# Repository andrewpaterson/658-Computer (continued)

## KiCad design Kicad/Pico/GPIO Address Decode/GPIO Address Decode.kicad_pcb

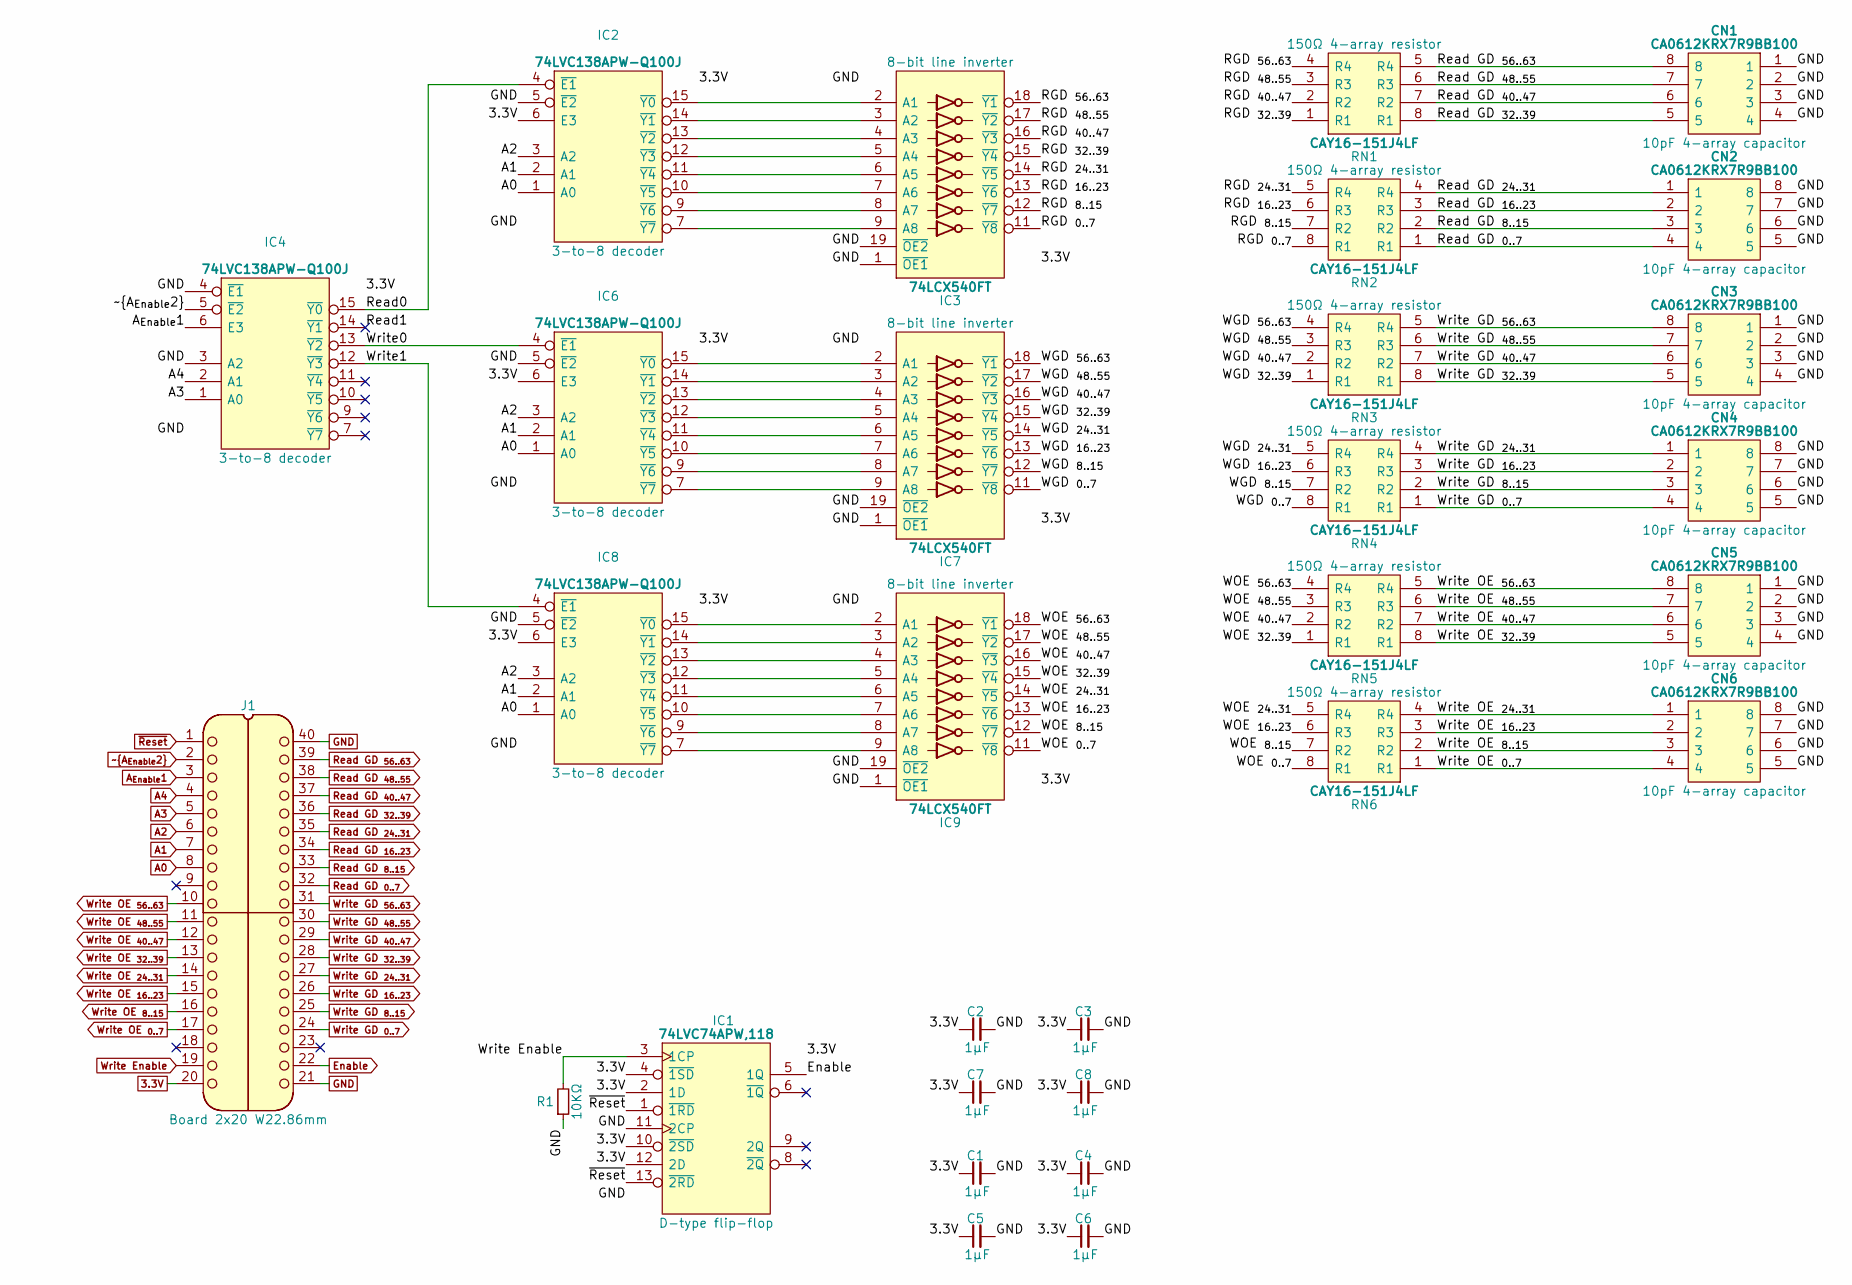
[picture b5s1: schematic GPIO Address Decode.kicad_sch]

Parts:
C1, C2, C3, C4, C5, C6, C7, C8: 1μF; C_0805
CN1, CN2, CN3, CN4, CN5, CN6: CA0612KRX7R9BB100; Manufacturer_Part_Number CA0612KRX7R9BB102; Mouser Part Number 603-CA612KRX7R9BB102
IC1: 74LVC74APW,118; SOP65P640X110-14N; Mouser Part Number 771-74LVC74APW-T
IC2, IC4, IC6, IC8: 74LVC138APW-Q100J; SOP65P640X110-16N; Mouser Part Number 771-74LVC138APWQ100J
IC3, IC7, IC9: 74LCX540FT; SOP65P640X120-20N; Manufacturer_Part_Number 74LCX540FT; Mouser Part Number 757-74LCX540FT
J1: Board 2x20 W22.86mm; DIP-40_Board_W22.86mm
R1: 10KΩ; R_0805
RN1, RN2, RN3, RN4, RN5, RN6: CAY16-151J4LF; CAY16-J4; Manufacturer_Part_Number CAY16-151J4LF; Mouser Part Number 652-CAY16-151J4LF

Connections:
3.3V: C1.1, C2.1, C3.1, C4.1, C5.1, C6.1, C7.1, C8.1, IC1.2 (1D), IC1.4 (~1SD), IC1.10 (~2SD), IC1.12 (2D), IC1.14 (3V), IC2.6 (E3), IC2.16 (3V), IC3.20 (3V), IC4.16 (3V), IC6.6 (E3), IC6.16 (3V), IC7.20 (3V), IC8.6 (E3), IC8.16 (3V), IC9.20 (3V), J1.20
/RGD _{0..7}: IC3.11 (~Y8), RN2.8 (R1)
/RGD _{8..15}: IC3.12 (~Y7), RN2.7 (R2)
/RGD _{16..23}: IC3.13 (~Y6), RN2.6 (R3)
/RGD _{24..31}: IC3.14 (~Y5), RN2.5 (R4)
/RGD _{32..39}: IC3.15 (~Y4), RN1.1 (R1)
/RGD _{40..47}: IC3.16 (~Y3), RN1.2 (R2)
/RGD _{48..55}: IC3.17 (~Y2), RN1.3 (R3)
/RGD _{56..63}: IC3.18 (~Y1), RN1.4 (R4)
/Read0: IC2.4 (~E1), IC4.15 (~Y0)
/Read1: IC4.14 (~Y1)
/WGD _{0..7}: IC7.11 (~Y8), RN4.8 (R1)
/WGD _{8..15}: IC7.12 (~Y7), RN4.7 (R2)
/WGD _{16..23}: IC7.13 (~Y6), RN4.6 (R3)
/WGD _{24..31}: IC7.14 (~Y5), RN4.5 (R4)
/WGD _{32..39}: IC7.15 (~Y4), RN3.1 (R1)
/WGD _{40..47}: IC7.16 (~Y3), RN3.2 (R2)
/WGD _{48..55}: IC7.17 (~Y2), RN3.3 (R3)
/WGD _{56..63}: IC7.18 (~Y1), RN3.4 (R4)
/WOE _{0..7}: IC9.11 (~Y8), RN6.8 (R1)
/WOE _{8..15}: IC9.12 (~Y7), RN6.7 (R2)
/WOE _{16..23}: IC9.13 (~Y6), RN6.6 (R3)
/WOE _{24..31}: IC9.14 (~Y5), RN6.5 (R4)
/WOE _{32..39}: IC9.15 (~Y4), RN5.1 (R1)
/WOE _{40..47}: IC9.16 (~Y3), RN5.2 (R2)
/WOE _{48..55}: IC9.17 (~Y2), RN5.3 (R3)
/WOE _{56..63}: IC9.18 (~Y1), RN5.4 (R4)
/Write0: IC4.13 (~Y2), IC6.4 (~E1)
/Write1: IC4.12 (~Y3), IC8.4 (~E1)
A0: IC2.1 (A0), IC6.1 (A0), IC8.1 (A0), J1.8
A1: IC2.2 (A1), IC6.2 (A1), IC8.2 (A1), J1.7
A2: IC2.3 (A2), IC6.3 (A2), IC8.3 (A2), J1.6
A3: IC4.1 (A0), J1.5
A4: IC4.2 (A1), J1.4
A_{Enable}1: IC4.6 (E3), J1.3
Enable: IC1.5 (1Q), J1.22
GND: C1.2, C2.2, C3.2, C4.2, C5.2, C6.2, C7.2, C8.2, CN1.1, CN1.2, CN1.3, CN1.4, CN2.5, CN2.6, CN2.7, CN2.8, CN3.1, CN3.2, CN3.3, CN3.4, CN4.5, CN4.6, CN4.7, CN4.8, CN5.1, CN5.2, CN5.3, CN5.4, CN6.5, CN6.6, CN6.7, CN6.8, IC1.7 (GND), IC1.11 (2CP), IC2.5 (~E2), IC2.8 (GND), IC3.1 (~OE1), IC3.10 (GND), IC3.19 (~OE2), IC4.3 (A2), IC4.4 (~E1), IC4.8 (GND), IC6.5 (~E2), IC6.8 (GND), IC7.1 (~OE1), IC7.10 (GND), IC7.19 (~OE2), IC8.5 (~E2), IC8.8 (GND), IC9.1 (~OE1), IC9.10 (GND), IC9.19 (~OE2), J1.21, J1.40, R1.1
unnamed: IC2.15 (~Y0), IC3.2 (A1)
unnamed: IC2.14 (~Y1), IC3.3 (A2)
unnamed: IC2.13 (~Y2), IC3.4 (A3)
unnamed: IC2.12 (~Y3), IC3.5 (A4)
unnamed: IC2.11 (~Y4), IC3.6 (A5)
unnamed: IC2.10 (~Y5), IC3.7 (A6)
unnamed: IC2.9 (~Y6), IC3.8 (A7)
unnamed: IC2.7 (~Y7), IC3.9 (A8)
unnamed: IC6.15 (~Y0), IC7.2 (A1)
unnamed: IC6.14 (~Y1), IC7.3 (A2)
unnamed: IC6.13 (~Y2), IC7.4 (A3)
unnamed: IC6.12 (~Y3), IC7.5 (A4)
unnamed: IC6.11 (~Y4), IC7.6 (A5)
unnamed: IC6.10 (~Y5), IC7.7 (A6)
unnamed: IC6.9 (~Y6), IC7.8 (A7)
unnamed: IC6.7 (~Y7), IC7.9 (A8)
unnamed: IC8.15 (~Y0), IC9.2 (A1)
unnamed: IC8.14 (~Y1), IC9.3 (A2)
unnamed: IC8.13 (~Y2), IC9.4 (A3)
unnamed: IC8.12 (~Y3), IC9.5 (A4)
unnamed: IC8.11 (~Y4), IC9.6 (A5)
unnamed: IC8.10 (~Y5), IC9.7 (A6)
unnamed: IC8.9 (~Y6), IC9.8 (A7)
unnamed: IC8.7 (~Y7), IC9.9 (A8)
Read GD _{0..7}: CN2.4, J1.32, RN2.1 (R1)
Read GD _{8..15}: CN2.3, J1.33, RN2.2 (R2)
Read GD _{16..23}: CN2.2, J1.34, RN2.3 (R3)
Read GD _{24..31}: CN2.1, J1.35, RN2.4 (R4)
Read GD _{32..39}: CN1.5, J1.36, RN1.8 (R1)
Read GD _{40..47}: CN1.6, J1.37, RN1.7 (R2)
Read GD _{48..55}: CN1.7, J1.38, RN1.6 (R3)
Read GD _{56..63}: CN1.8, J1.39, RN1.5 (R4)
Write Enable: IC1.3 (1CP), J1.19, R1.2
Write GD _{0..7}: CN4.4, J1.24, RN4.1 (R1)
Write GD _{8..15}: CN4.3, J1.25, RN4.2 (R2)
Write GD _{16..23}: CN4.2, J1.26, RN4.3 (R3)
Write GD _{24..31}: CN4.1, J1.27, RN4.4 (R4)
Write GD _{32..39}: CN3.5, J1.28, RN3.8 (R1)
Write GD _{40..47}: CN3.6, J1.29, RN3.7 (R2)
Write GD _{48..55}: CN3.7, J1.30, RN3.6 (R3)
Write GD _{56..63}: CN3.8, J1.31, RN3.5 (R4)
Write OE _{0..7}: CN6.4, J1.17, RN6.1 (R1)
Write OE _{8..15}: CN6.3, J1.16, RN6.2 (R2)
Write OE _{16..23}: CN6.2, J1.15, RN6.3 (R3)
Write OE _{24..31}: CN6.1, J1.14, RN6.4 (R4)
Write OE _{32..39}: CN5.5, J1.13, RN5.8 (R1)
Write OE _{40..47}: CN5.6, J1.12, RN5.7 (R2)
Write OE _{48..55}: CN5.7, J1.11, RN5.6 (R3)
Write OE _{56..63}: CN5.8, J1.10, RN5.5 (R4)
~A_{Enable2}: IC4.5 (~E2), J1.2
~Reset: IC1.1 (~1RD), IC1.13 (~2RD), J1.1

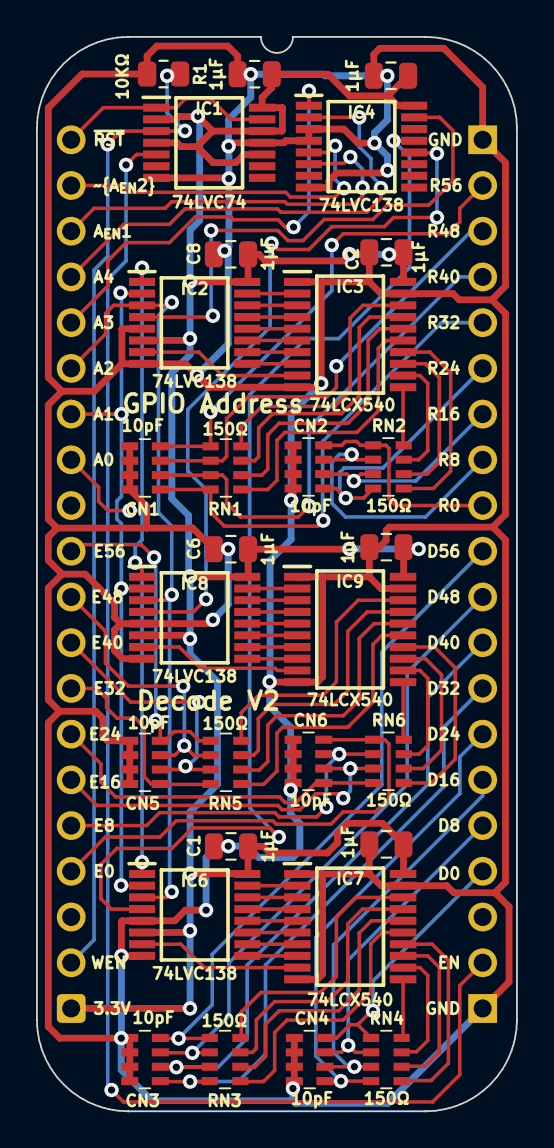
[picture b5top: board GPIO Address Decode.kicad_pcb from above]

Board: 2 copper layers, 26.7 x 59.7 mm, 30 parts (0 on the bottom side), 87 nets.

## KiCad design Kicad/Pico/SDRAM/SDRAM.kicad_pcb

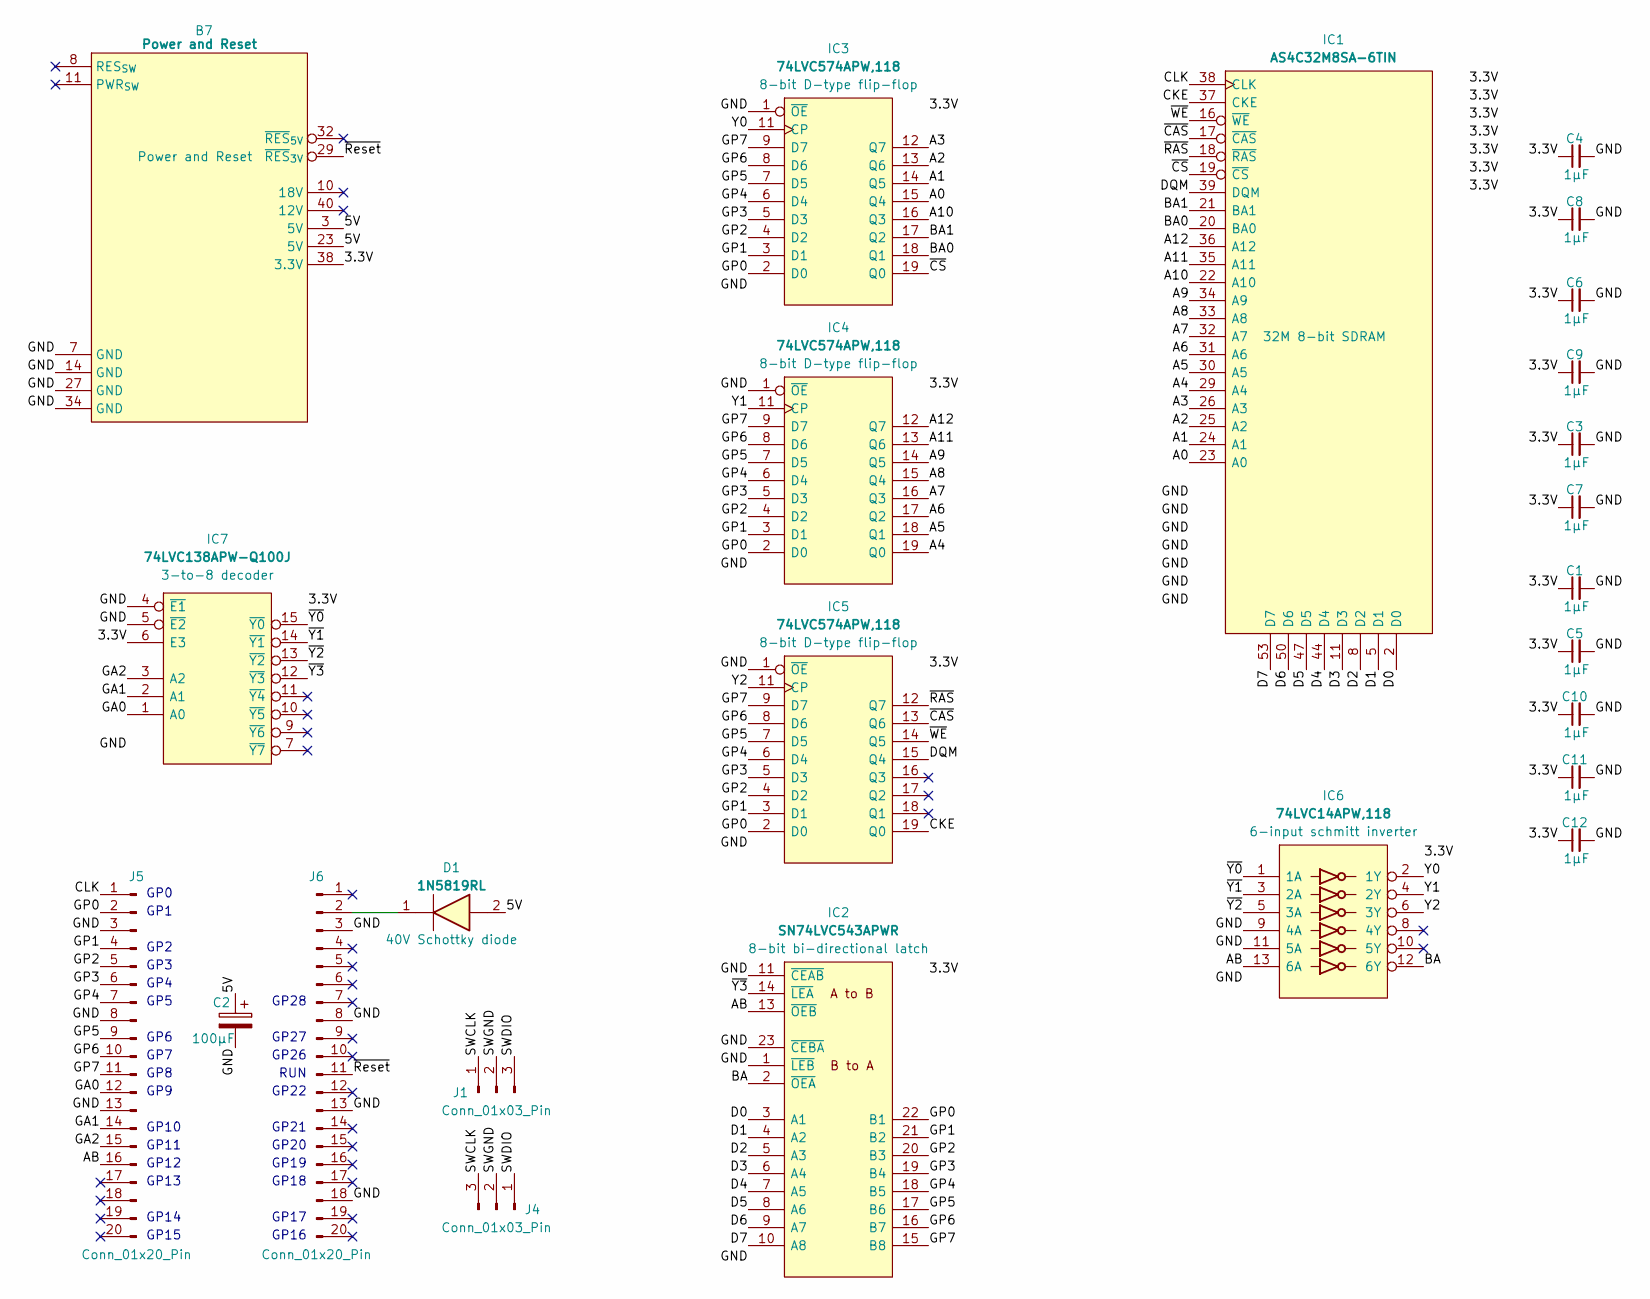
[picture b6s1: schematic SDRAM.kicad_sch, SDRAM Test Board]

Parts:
B7: Power and Reset; HCP65_Power_and_Reset
C1, C3, C4, C5, C6, C7, C8, C9, C10, C11, C12: 1μF; C_0805
C2: 100μF; CP_Radial_D6.3mm_P2.50mm
D1: 1N5819RL; DIOAD1414W86L464D238; Manufacturer_Part_Number 1N5819RL; Mouser Part Number 511-1N5819-TR
IC1: AS4C32M8SA-6TIN; SOP80P1176X120-54N; Manufacturer_Part_Number AS4C32M8SA-6TIN
IC2: SN74LVC543APWR; SOP65P640X120-24N; Mouser Part Number 595-SN74LVC543APWR
IC3, IC4, IC5: 74LVC574APW,118; SOP65P640X110-20N; Manufacturer_Part_Number 74LVC574APW,118; Mouser Part Number 771-74LVC574APW-T
IC6: 74LVC14APW,118; SOP65P640X110-14N; Manufacturer_Part_Number 74LVC14APW,118; Mouser Part Number 771-74LVC14APW-T
IC7: 74LVC138APW-Q100J; SOP65P640X110-16N; Mouser Part Number 771-74LVC138APWQ100J
J1: Conn_01x03_Pin; PinSocket_1x03_P2.54mm_Vertical
J4: Conn_01x03_Pin; PinHeader_1x03_P2.54mm_Horizontal
J5, J6: Conn_01x20_Pin; PinSocket_1x20_P2.54mm_Vertical

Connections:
/3.3V: B7.38 (3.3V), C1.1, C3.1, C4.1, C5.1, C6.1, C7.1, C8.1, C9.1, C10.1, C11.1, C12.1, IC1.1 (3V), IC1.3 (VDDQ), IC1.9 (VDDQ), IC1.14 (3V), IC1.27 (3V), IC1.43 (VDDQ), IC1.49 (VDDQ), IC2.24 (3V), IC3.20 (3V), IC4.20 (3V), IC5.20 (3V), IC6.14 (3V), IC7.6 (E3), IC7.16 (3V)
/5V: B7.3 (5V), B7.23 (5V), C2.1, D1.2
/A0: IC1.23 (A0), IC3.15 (Q4)
/A1: IC1.24 (A1), IC3.14 (Q5)
/A2: IC1.25 (A2), IC3.13 (Q6)
/A3: IC1.26 (A3), IC3.12 (Q7)
/A4: IC1.29 (A4), IC4.19 (Q0)
/A5: IC1.30 (A5), IC4.18 (Q1)
/A6: IC1.31 (A6), IC4.17 (Q2)
/A7: IC1.32 (A7), IC4.16 (Q3)
/A8: IC1.33 (A8), IC4.15 (Q4)
/A9: IC1.34 (A9), IC4.14 (Q5)
/A10: IC1.22 (A10), IC3.16 (Q3)
/A11: IC1.35 (A11), IC4.13 (Q6)
/A12: IC1.36 (A12), IC4.12 (Q7)
/AB: IC2.13 (~OEB), IC6.13 (6A), J5.16
/BA: IC2.2 (~OEA), IC6.12 (6Y)
/BA0: IC1.20 (BA0), IC3.18 (Q1)
/BA1: IC1.21 (BA1), IC3.17 (Q2)
/CKE: IC1.37 (CKE), IC5.19 (Q0)
/CLK: IC1.38 (CLK), J5.1
/D0: IC1.2 (D0), IC2.3 (A1)
/D1: IC1.5 (D1), IC2.4 (A2)
/D2: IC1.8 (D2), IC2.5 (A3)
/D3: IC1.11 (D3), IC2.6 (A4)
/D4: IC1.44 (D4), IC2.7 (A5)
/D5: IC1.47 (D5), IC2.8 (A6)
/D6: IC1.50 (D6), IC2.9 (A7)
/D7: IC1.53 (D7), IC2.10 (A8)
/DQM: IC1.39 (DQM), IC5.15 (Q4)
/GA0: IC7.1 (A0), J5.12
/GA1: IC7.2 (A1), J5.14
/GA2: IC7.3 (A2), J5.15
/GND: B7.7 (GND), B7.14 (GND), B7.27 (GND), B7.34 (GND), C1.2, C2.2, C3.2, C4.2, C5.2, C6.2, C7.2, C8.2, C9.2, C10.2, C11.2, C12.2, IC1.6 (VSSQ), IC1.12 (VSSQ), IC1.28 (GND), IC1.41 (GND), IC1.46 (VSSQ), IC1.52 (VSSQ), IC1.54 (GND), IC2.1 (~LEB), IC2.11 (~CEAB), IC2.12 (GND), IC2.23 (~CEBA), IC3.1 (~OE), IC3.10 (GND), IC4.1 (~OE), IC4.10 (GND), IC5.1 (~OE), IC5.10 (GND), IC6.7 (GND), IC6.9 (4A), IC6.11 (5A), IC7.4 (~E1), IC7.5 (~E2), IC7.8 (GND), J5.3, J5.8, J5.13, J6.3, J6.8, J6.13, J6.18
/GP0: IC2.22 (B1), IC3.2 (D0), IC4.2 (D0), IC5.2 (D0), J5.2
/GP1: IC2.21 (B2), IC3.3 (D1), IC4.3 (D1), IC5.3 (D1), J5.4
/GP2: IC2.20 (B3), IC3.4 (D2), IC4.4 (D2), IC5.4 (D2), J5.5
/GP3: IC2.19 (B4), IC3.5 (D3), IC4.5 (D3), IC5.5 (D3), J5.6
/GP4: IC2.18 (B5), IC3.6 (D4), IC4.6 (D4), IC5.6 (D4), J5.7
/GP5: IC2.17 (B6), IC3.7 (D5), IC4.7 (D5), IC5.7 (D5), J5.9
/GP6: IC2.16 (B7), IC3.8 (D6), IC4.8 (D6), IC5.8 (D6), J5.10
/GP7: IC2.15 (B8), IC3.9 (D7), IC4.9 (D7), IC5.9 (D7), J5.11
/SWCLK: J1.1, J4.3
/SWDIO: J1.3, J4.1
/SWGND: J1.2, J4.2
/Y0: IC3.11 (CP), IC6.2 (1Y)
/Y1: IC4.11 (CP), IC6.4 (2Y)
/Y2: IC5.11 (CP), IC6.6 (3Y)
/~CAS: IC1.17 (~CAS), IC5.13 (Q6)
/~CS: IC1.19 (~CS), IC3.19 (Q0)
/~RAS: IC1.18 (~RAS), IC5.12 (Q7)
/~Reset: B7.29 (~RES_{3V}), J6.11
/~WE: IC1.16 (~WE), IC5.14 (Q5)
/~Y0: IC6.1 (1A), IC7.15 (~Y0)
/~Y1: IC6.3 (2A), IC7.14 (~Y1)
/~Y2: IC6.5 (3A), IC7.13 (~Y2)
/~Y3: IC2.14 (~LEA), IC7.12 (~Y3)
unnamed: D1.1, J6.2

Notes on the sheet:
GP15
GP7
GP27
GP5
GP11
GP26
GP8
GP28
GP16
GP22
GP14
GP4
GP21
GP20
GP9
GP12
GP17
GP3
RUN
GP10
GP1
GP18
GP2
GP6
GP13
GP0
GP19

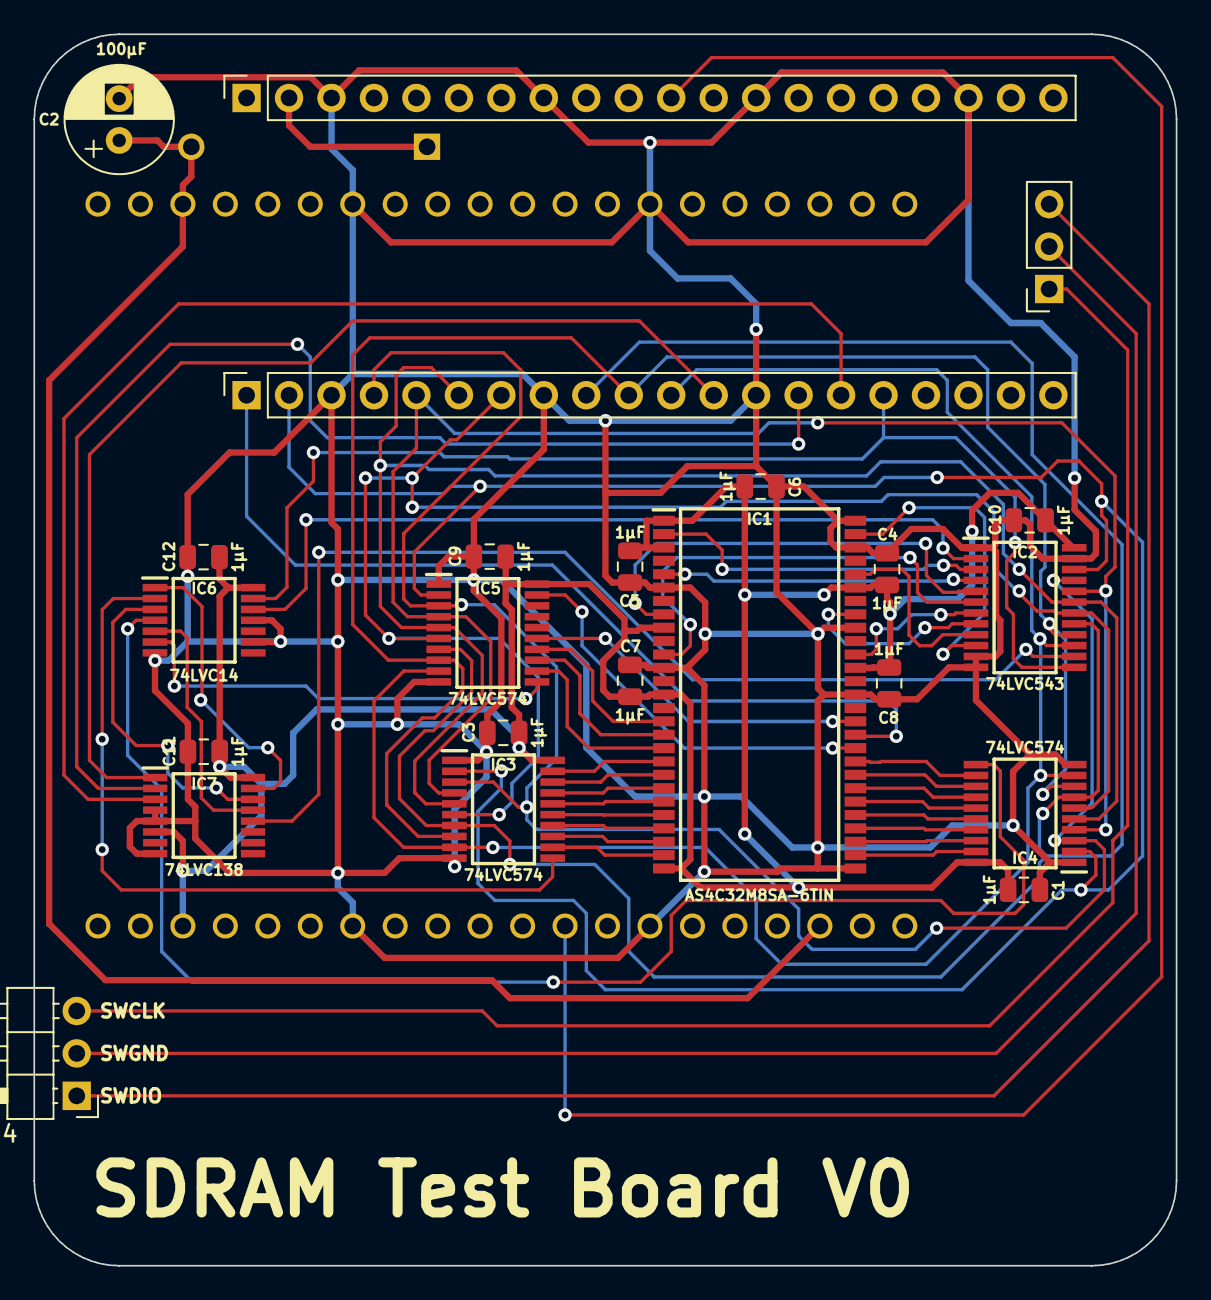
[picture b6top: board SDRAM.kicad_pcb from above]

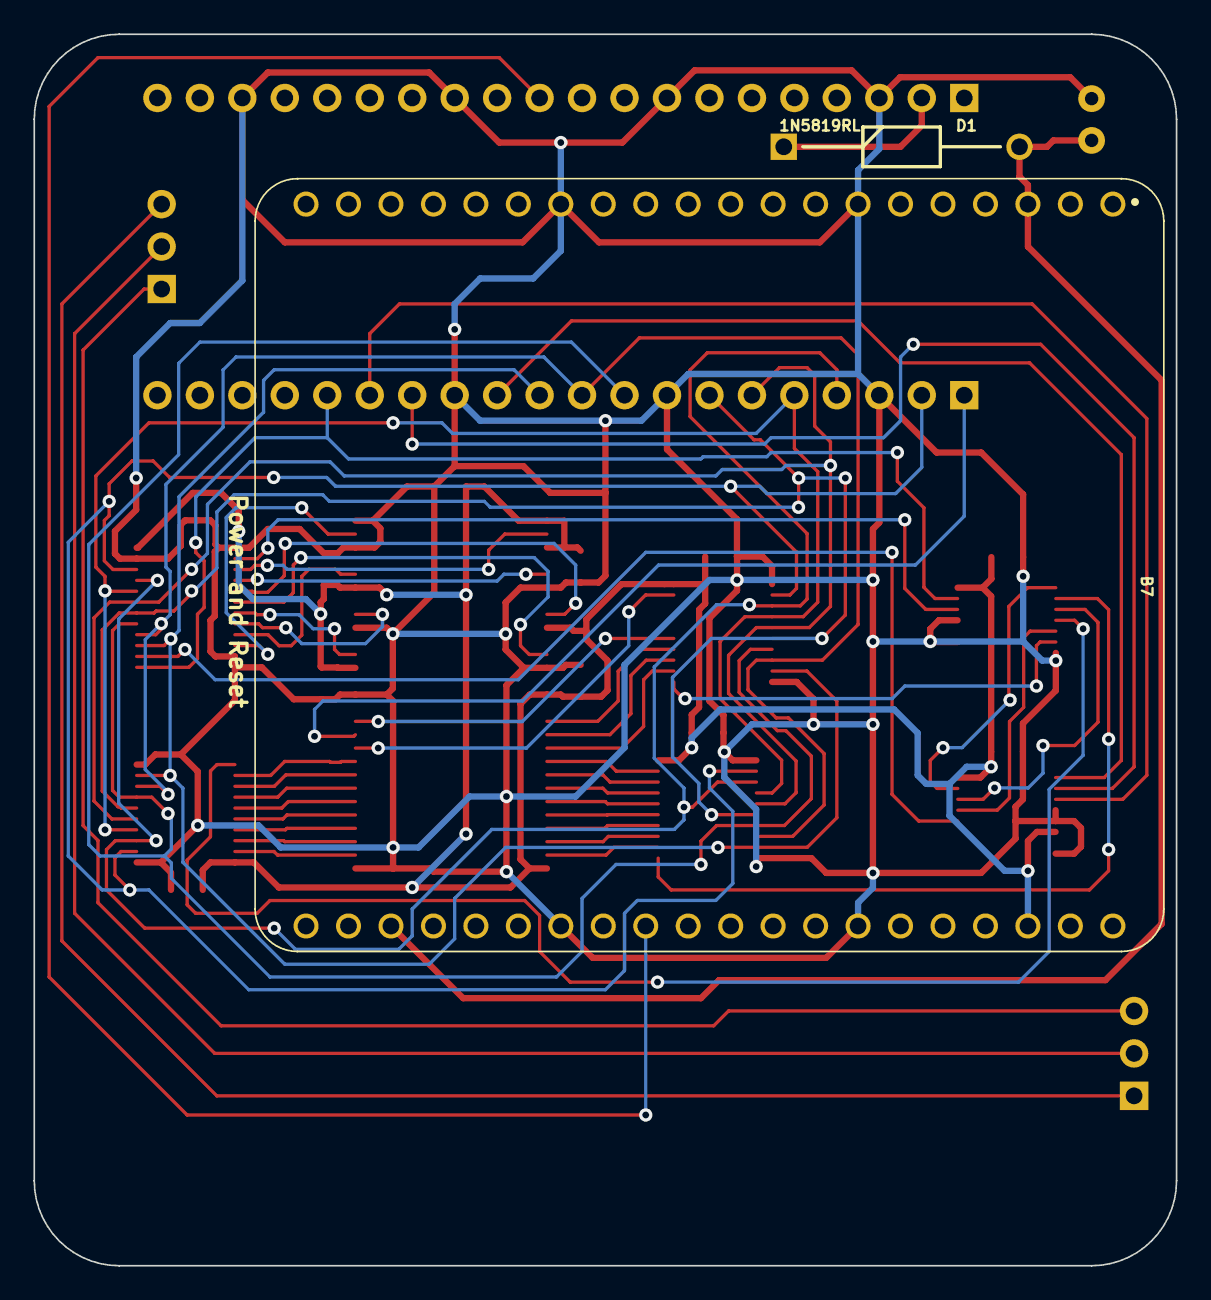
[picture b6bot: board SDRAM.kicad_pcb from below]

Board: 2 copper layers, 68.3 x 73.7 mm, 25 parts (2 on the bottom side), 58 nets.

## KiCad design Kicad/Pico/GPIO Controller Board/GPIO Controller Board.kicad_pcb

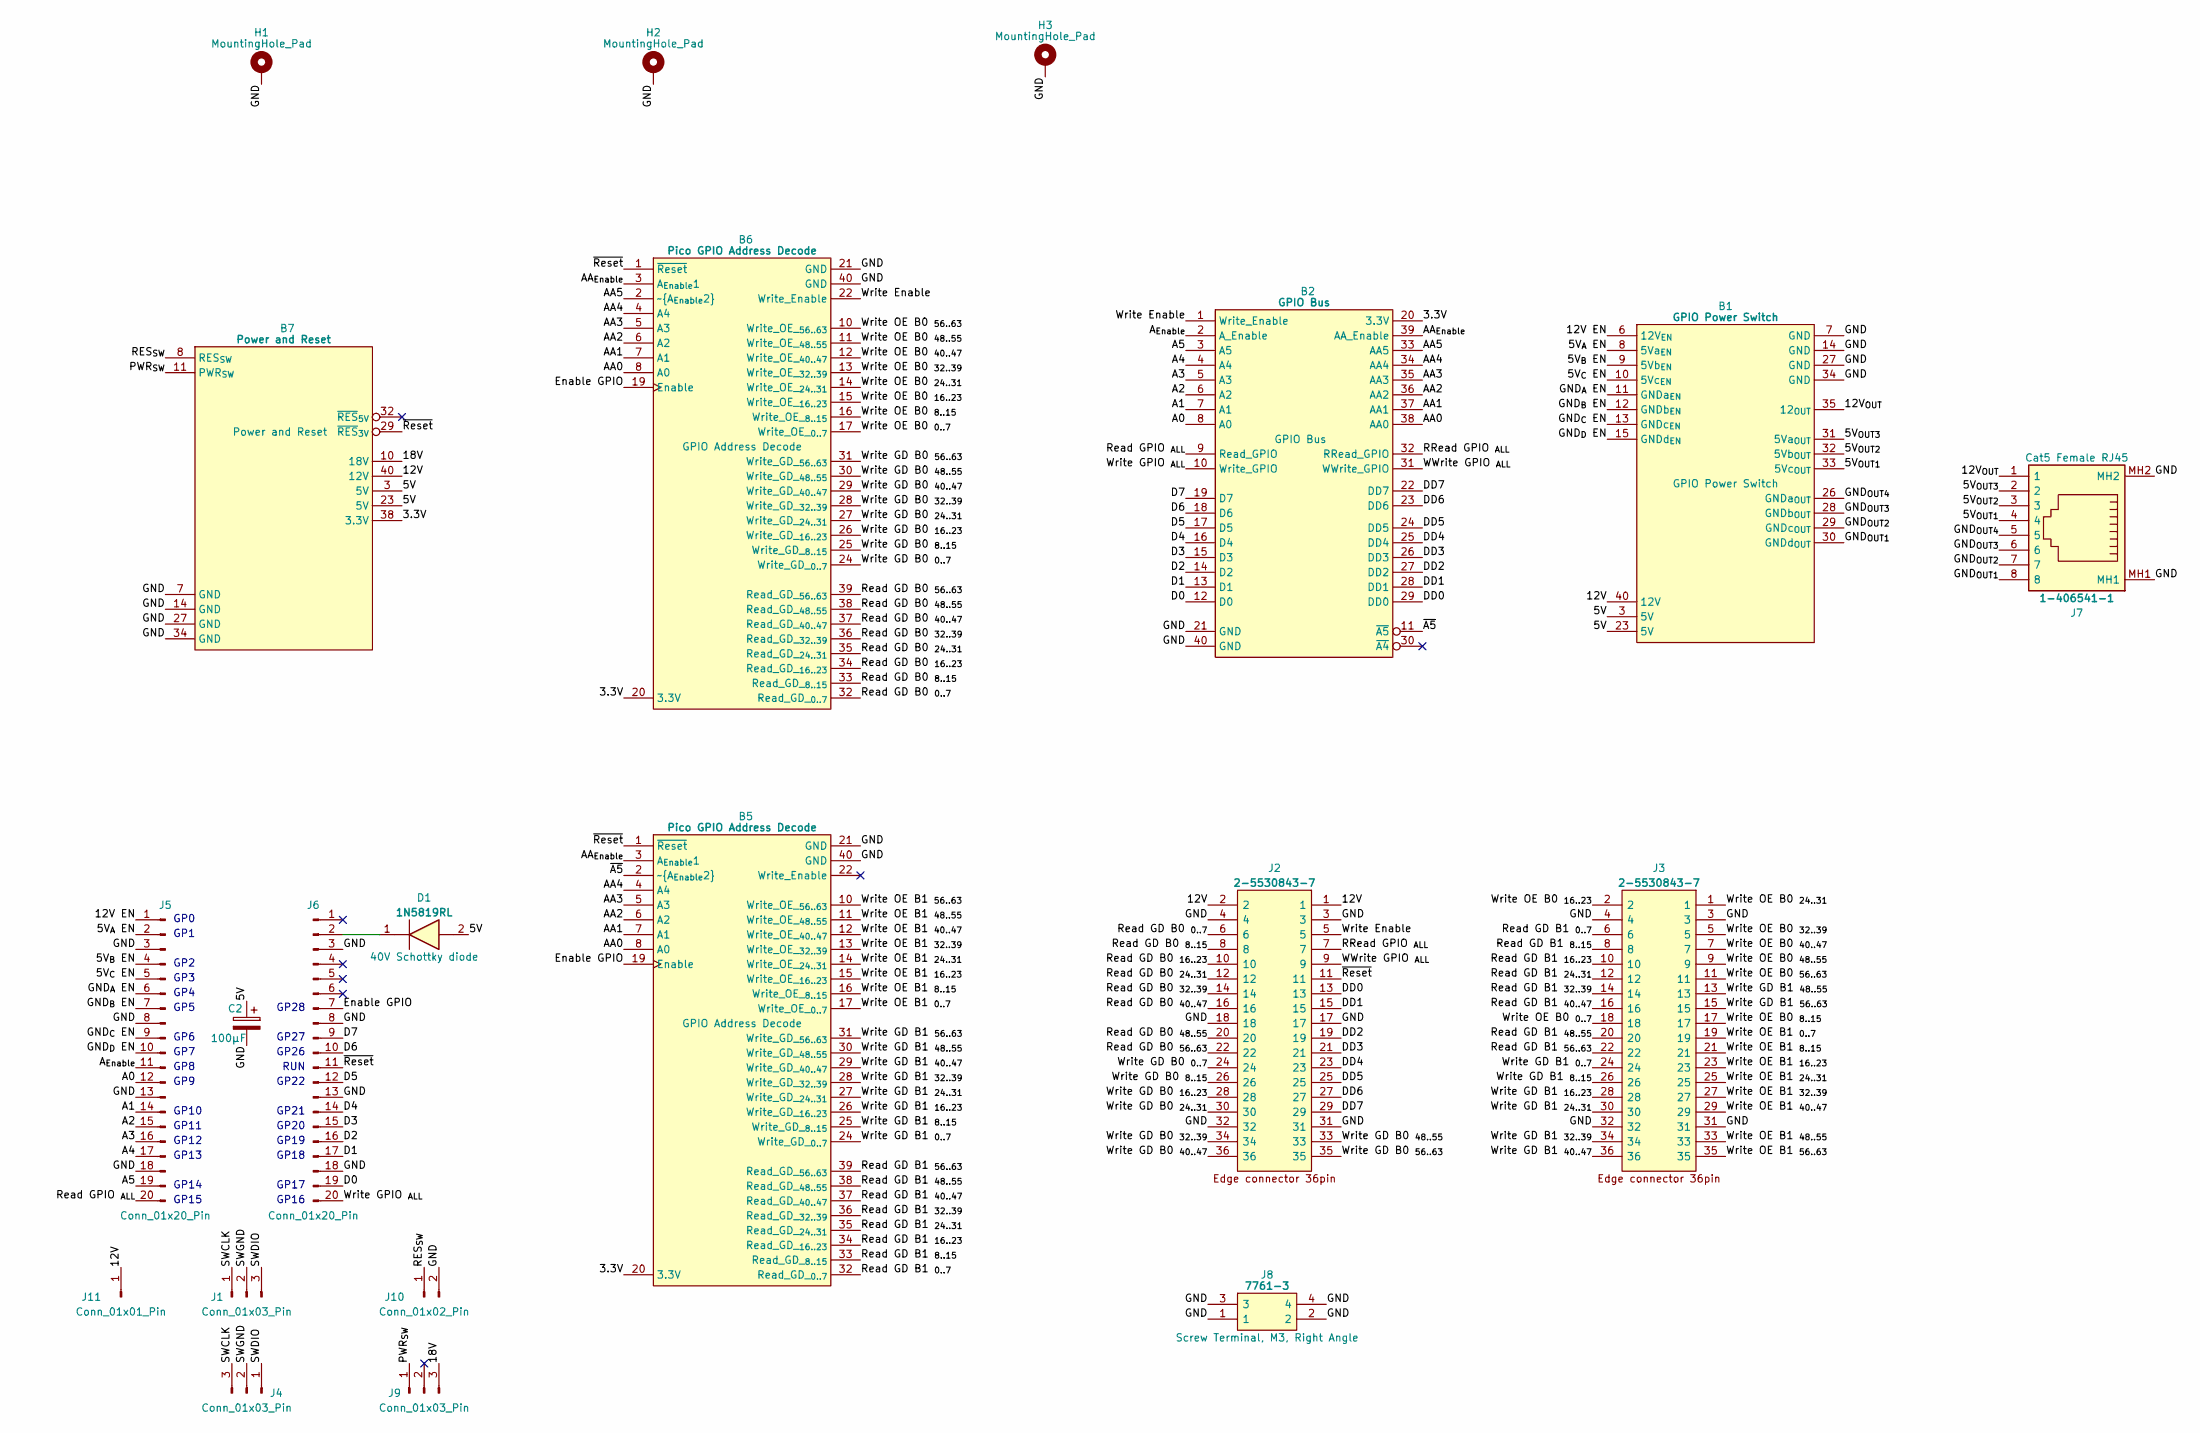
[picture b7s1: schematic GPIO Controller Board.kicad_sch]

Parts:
B1: GPIO Power Switch; HCP65_GPIO_Power_Switch
B2: GPIO Bus; HCP65_GPIO_Bus
B5, B6: Pico GPIO Address Decode; HCP65_GPIO_Address_Decode
B7: Power and Reset; HCP65_Power_and_Reset
C2: 100μF; CP_Radial_D6.3mm_P2.50mm
D1: 1N5819RL; DIOAD1414W86L464D238; Manufacturer_Part_Number 1N5819RL; Mouser Part Number 511-1N5819-TR
H1, H2, H3: MountingHole_Pad; MountingHole_3.2mm_M3_Pad
J1: Conn_01x03_Pin; PinSocket_1x03_P2.54mm_Vertical
J2, J3: 2-5530843-7; 36pin Edge Connector; Manufacturer_Part_Number 2-5530843-7; Mouser Part Number 571-2-5530843-7
J4: Conn_01x03_Pin; PinHeader_1x03_P2.54mm_Horizontal
J5, J6: Conn_01x20_Pin; PinSocket_1x20_P2.54mm_Vertical
J7: 1-406541-1; 1-406541-1_1; Manufacturer_Part_Number 1-406541-1; Mouser Part Number 571-1-406541-1
J8: 7761-3; 77613; Manufacturer_Part_Number 7761-3
J9: Conn_01x03_Pin; PinHeader_1x03_P2.54mm_Vertical
J10: Conn_01x02_Pin; PinHeader_1x02_P2.54mm_Vertical
J11: Conn_01x01_Pin; PinSocket_1x01_P2.54mm_Vertical

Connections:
/3.3V: B2.20 (3.3V), B5.20 (3.3V), B6.20 (3.3V), B7.38 (3.3V)
/5V: B1.3 (5V), B1.23 (5V), B7.3 (5V), B7.23 (5V), C2.1, D1.2
/5V_{A} EN: B1.8 (5Va_{EN}), J5.2
/5V_{B} EN: B1.9 (5Vb_{EN}), J5.4
/5V_{C} EN: B1.10 (5Vc_{EN}), J5.5
/5V_{OUT1}: B1.33 (5Vc_{OUT}), J7.4
/5V_{OUT2}: B1.32 (5Vb_{OUT}), J7.3
/5V_{OUT3}: B1.31 (5Va_{OUT}), J7.2
/12V: B1.40 (12V), B7.40 (12V), J2.1, J2.2, J11.1
/12V EN: B1.6 (12V_{EN}), J5.1
/12V_{OUT}: B1.35 (12_{OUT}), J7.1
/18V: B7.10 (18V), J9.3
/A0: B2.8 (A0), J5.12
/A1: B2.7 (A1), J5.14
/A2: B2.6 (A2), J5.15
/A3: B2.5 (A3), J5.16
/A4: B2.4 (A4), J5.17
/A5: B2.3 (A5), J5.19
/AA0: B2.38 (AA0), B5.8 (A0), B6.8 (A0)
/AA1: B2.37 (AA1), B5.7 (A1), B6.7 (A1)
/AA2: B2.36 (AA2), B5.6 (A2), B6.6 (A2)
/AA3: B2.35 (AA3), B5.5 (A3), B6.5 (A3)
/AA4: B2.34 (AA4), B5.4 (A4), B6.4 (A4)
/AA5: B2.33 (AA5), B6.2 (~A_{Enable2})
/AA_{Enable}: B2.39 (AA_Enable), B5.3 (A_{Enable}1), B6.3 (A_{Enable}1)
/A_{Enable}: B2.2 (A_Enable), J5.11
/D0: B2.12 (D0), J6.19
/D1: B2.13 (D1), J6.17
/D2: B2.14 (D2), J6.16
/D3: B2.15 (D3), J6.15
/D4: B2.16 (D4), J6.14
/D5: B2.17 (D5), J6.12
/D6: B2.18 (D6), J6.10
/D7: B2.19 (D7), J6.9
/DD0: B2.29 (DD0), J2.13
/DD1: B2.28 (DD1), J2.15
/DD2: B2.27 (DD2), J2.19
/DD3: B2.26 (DD3), J2.21
/DD4: B2.25 (DD4), J2.23
/DD5: B2.24 (DD5), J2.25
/DD6: B2.23 (DD6), J2.27
/DD7: B2.22 (DD7), J2.29
/Enable GPIO: B5.19 (Enable), B6.19 (Enable), J6.7
/GND: B1.7 (GND), B1.14 (GND), B1.27 (GND), B1.34 (GND), B2.21 (GND), B2.40 (GND), B5.21 (GND), B5.40 (GND), B6.21 (GND), B6.40 (GND), B7.7 (GND), B7.14 (GND), B7.27 (GND), B7.34 (GND), C2.2, H1.1, H2.1, H3.1, J2.3, J2.4, J2.17, J2.18, J2.31, J2.32, J3.3, J3.4, J3.31, J3.32, J5.3, J5.8, J5.13, J5.18, J6.3, J6.8, J6.13, J6.18, J7.MH1, J7.MH2, J8.1, J8.2, J8.3, J8.4, J10.2
/GND_{A} EN: B1.11 (GNDa_{EN}), J5.6
/GND_{B} EN: B1.12 (GNDb_{EN}), J5.7
/GND_{C} EN: B1.13 (GNDc_{EN}), J5.9
/GND_{D} EN: B1.15 (GNDd_{EN}), J5.10
/GND_{OUT1}: B1.30 (GNDd_{OUT}), J7.8
/GND_{OUT2}: B1.29 (GNDc_{OUT}), J7.7
/GND_{OUT3}: B1.28 (GNDb_{OUT}), J7.6
/GND_{OUT4}: B1.26 (GNDa_{OUT}), J7.5
/PWR_{SW}: B7.11 (PWR_{SW}), J9.1
/RES_{SW}: B7.8 (RES_{SW}), J10.1
/RRead GPIO _{ALL}: B2.32 (RRead_GPIO), J2.7
/Read GD B0 _{0..7}: B6.32 (Read_GD__{0..7}), J2.6
/Read GD B0 _{8..15}: B6.33 (Read_GD__{8..15}), J2.8
/Read GD B0 _{16..23}: B6.34 (Read_GD__{16..23}), J2.10
/Read GD B0 _{24..31}: B6.35 (Read_GD__{24..31}), J2.12
/Read GD B0 _{32..39}: B6.36 (Read_GD__{32..39}), J2.14
/Read GD B0 _{40..47}: B6.37 (Read_GD__{40..47}), J2.16
/Read GD B0 _{48..55}: B6.38 (Read_GD__{48..55}), J2.20
/Read GD B0 _{56..63}: B6.39 (Read_GD__{56..63}), J2.22
/Read GD B1 _{0..7}: B5.32 (Read_GD__{0..7}), J3.6
/Read GD B1 _{8..15}: B5.33 (Read_GD__{8..15}), J3.8
/Read GD B1 _{16..23}: B5.34 (Read_GD__{16..23}), J3.10
/Read GD B1 _{24..31}: B5.35 (Read_GD__{24..31}), J3.12
/Read GD B1 _{32..39}: B5.36 (Read_GD__{32..39}), J3.14
/Read GD B1 _{40..47}: B5.37 (Read_GD__{40..47}), J3.16
/Read GD B1 _{48..55}: B5.38 (Read_GD__{48..55}), J3.20
/Read GD B1 _{56..63}: B5.39 (Read_GD__{56..63}), J3.22
/Read GPIO _{ALL}: B2.9 (Read_GPIO), J5.20
/SWCLK: J1.1, J4.3
/SWDIO: J1.3, J4.1
/SWGND: J1.2, J4.2
/WWrite GPIO _{ALL}: B2.31 (WWrite_GPIO), J2.9
/Write Enable: B2.1 (Write_Enable), B6.22 (Write_Enable), J2.5
/Write GD B0 _{0..7}: B6.24 (Write_GD__{0..7}), J2.24
/Write GD B0 _{8..15}: B6.25 (Write_GD__{8..15}), J2.26
/Write GD B0 _{16..23}: B6.26 (Write_GD__{16..23}), J2.28
/Write GD B0 _{24..31}: B6.27 (Write_GD__{24..31}), J2.30
/Write GD B0 _{32..39}: B6.28 (Write_GD__{32..39}), J2.34
/Write GD B0 _{40..47}: B6.29 (Write_GD__{40..47}), J2.36
/Write GD B0 _{48..55}: B6.30 (Write_GD__{48..55}), J2.33
/Write GD B0 _{56..63}: B6.31 (Write_GD__{56..63}), J2.35
/Write GD B1 _{0..7}: B5.24 (Write_GD__{0..7}), J3.24
/Write GD B1 _{8..15}: B5.25 (Write_GD__{8..15}), J3.26
/Write GD B1 _{16..23}: B5.26 (Write_GD__{16..23}), J3.28
/Write GD B1 _{24..31}: B5.27 (Write_GD__{24..31}), J3.30
/Write GD B1 _{32..39}: B5.28 (Write_GD__{32..39}), J3.34
/Write GD B1 _{40..47}: B5.29 (Write_GD__{40..47}), J3.36
/Write GD B1 _{48..55}: B5.30 (Write_GD__{48..55}), J3.13
/Write GD B1 _{56..63}: B5.31 (Write_GD__{56..63}), J3.15
/Write GPIO _{ALL}: B2.10 (Write_GPIO), J6.20
/Write OE B0 _{0..7}: B6.17 (Write_OE__{0..7}), J3.18
/Write OE B0 _{8..15}: B6.16 (Write_OE__{8..15}), J3.17
/Write OE B0 _{16..23}: B6.15 (Write_OE__{16..23}), J3.2
/Write OE B0 _{24..31}: B6.14 (Write_OE__{24..31}), J3.1
/Write OE B0 _{32..39}: B6.13 (Write_OE__{32..39}), J3.5
/Write OE B0 _{40..47}: B6.12 (Write_OE__{40..47}), J3.7
/Write OE B0 _{48..55}: B6.11 (Write_OE__{48..55}), J3.9
/Write OE B0 _{56..63}: B6.10 (Write_OE__{56..63}), J3.11
/Write OE B1 _{0..7}: B5.17 (Write_OE__{0..7}), J3.19
/Write OE B1 _{8..15}: B5.16 (Write_OE__{8..15}), J3.21
/Write OE B1 _{16..23}: B5.15 (Write_OE__{16..23}), J3.23
/Write OE B1 _{24..31}: B5.14 (Write_OE__{24..31}), J3.25
/Write OE B1 _{32..39}: B5.13 (Write_OE__{32..39}), J3.27
/Write OE B1 _{40..47}: B5.12 (Write_OE__{40..47}), J3.29
/Write OE B1 _{48..55}: B5.11 (Write_OE__{48..55}), J3.33
/Write OE B1 _{56..63}: B5.10 (Write_OE__{56..63}), J3.35
/~A5: B2.11 (~A5), B5.2 (~A_{Enable2})
/~Reset: B5.1 (~Reset), B6.1 (~Reset), B7.29 (~RES_{3V}), J2.11, J6.11
unnamed: D1.1, J6.2

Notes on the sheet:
GP15
GP7
GP27
GP5
GP11
GP26
GP8
GP28
GP16
GP22
GP14
GP4
GP21
GP20
GP9
GP12
GP17
GP3
RUN
GP10
GP1
GP18
GP2
GP6
GP13
GP0
GP19

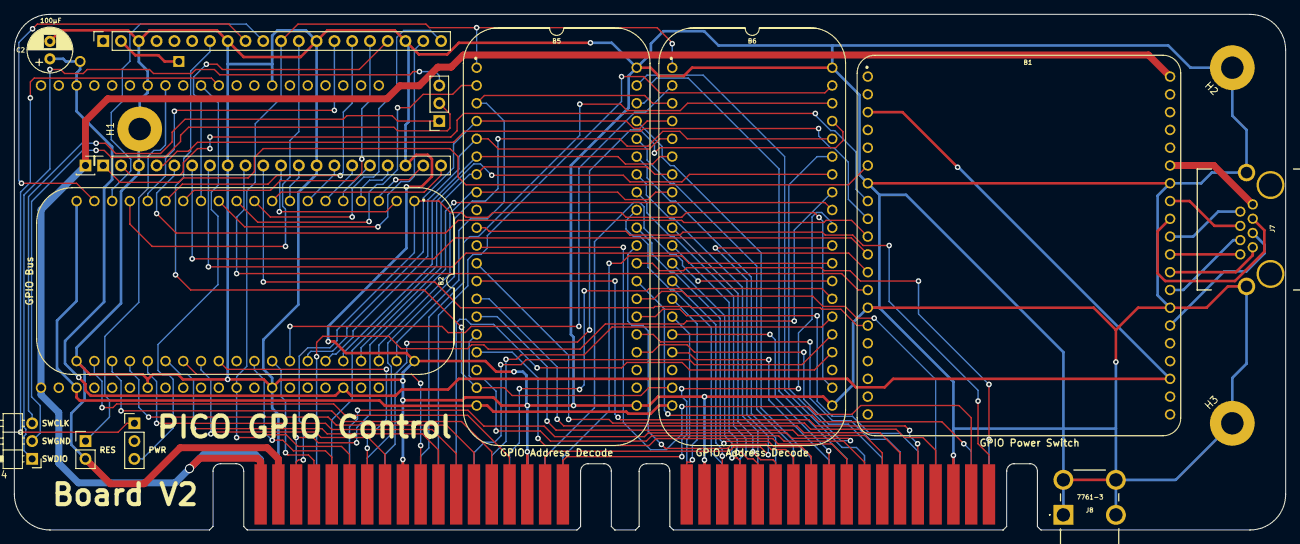
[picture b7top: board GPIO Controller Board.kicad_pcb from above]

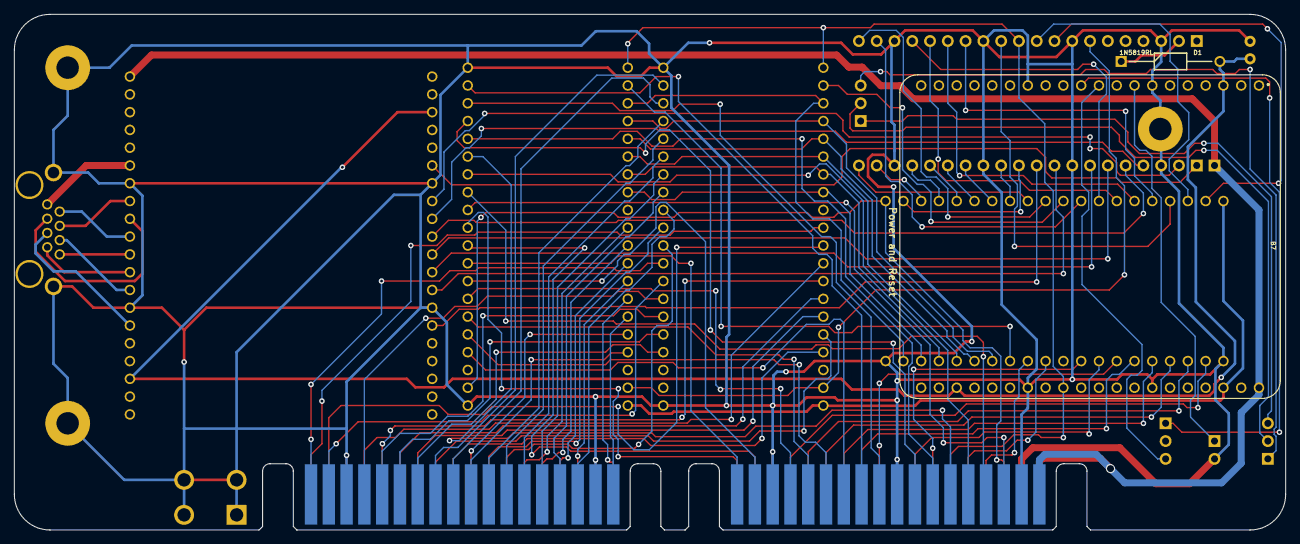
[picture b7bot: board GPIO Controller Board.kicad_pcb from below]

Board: 2 copper layers, 181.6 x 73.7 mm, 21 parts (2 on the bottom side), 113 nets.
